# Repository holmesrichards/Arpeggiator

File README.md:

# ArpeggiatorModule
Code and hardware for Kosmo/Eurorack arpeggiator module

This is an arpeggiator based on a variant of the [dacarduino](https://github.com/holmesrichards/dacarduino) board. As such it uses the dacarduino library as well as the Arpeggiator library in this repository.

Design is for Kosmo format module but the PCB and code would work equally well for a Eurorack version. It would just need a smaller front panel. Shorter anyway, maybe wider.

THIS IS A WORK IN PROGRESS.

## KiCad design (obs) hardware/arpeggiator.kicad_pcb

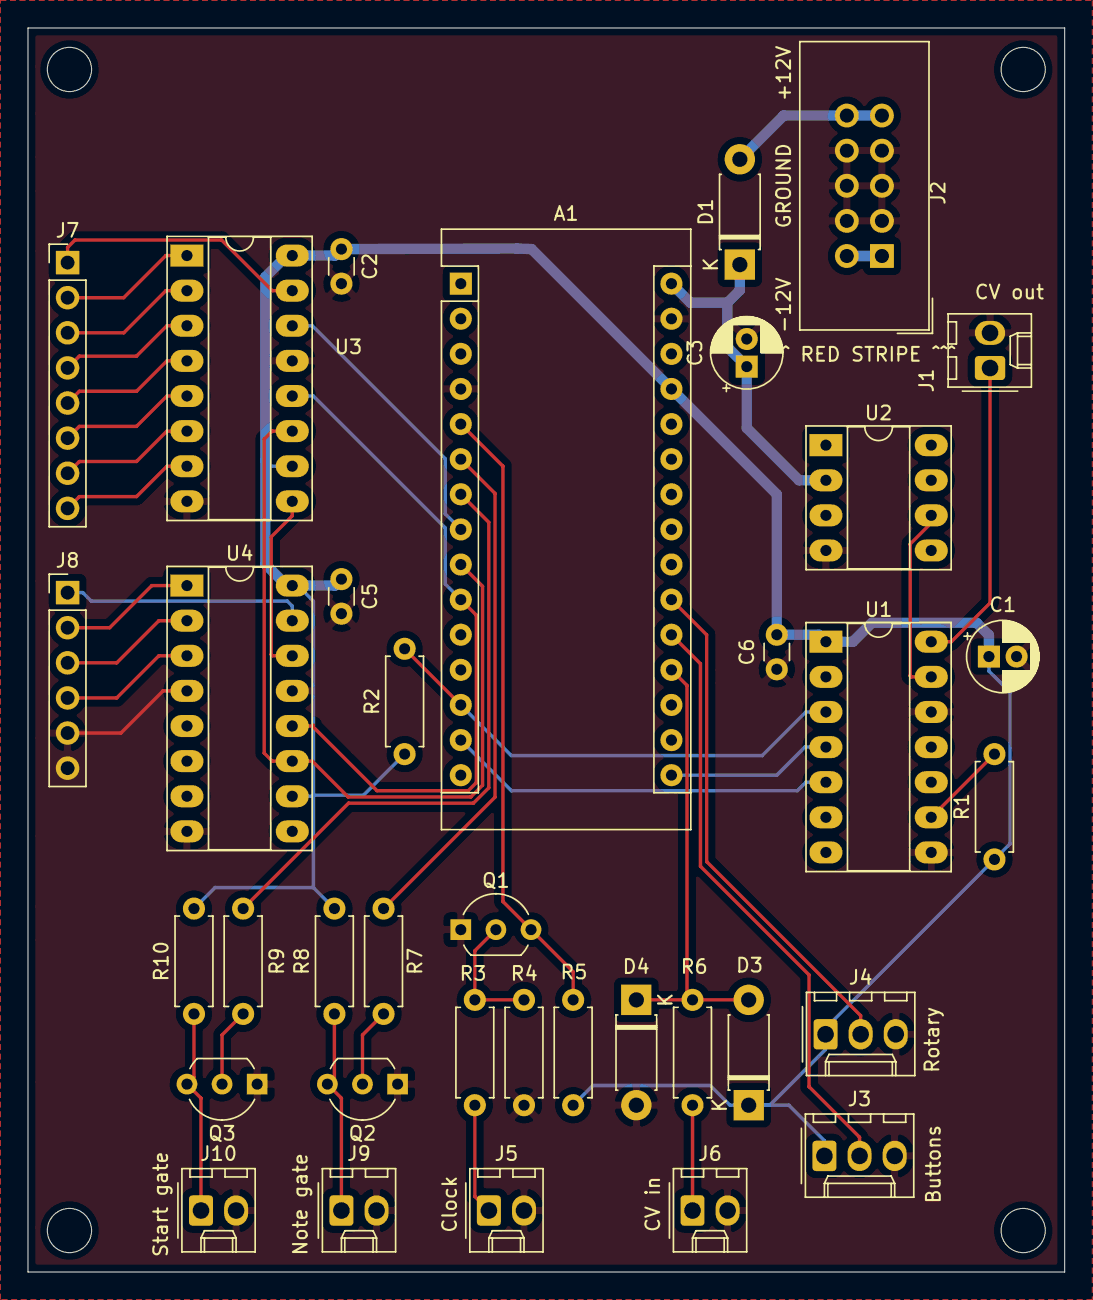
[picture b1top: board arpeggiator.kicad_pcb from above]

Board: 2 copper layers, 75.0 x 90.0 mm, 40 parts (0 on the bottom side), 41 nets.

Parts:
A1: Arduino_Nano_v3.x 5V; Arduino_Nano
C1, C3: 10uF; CP_Radial_D5.0mm_P2.00mm
C2, C5, C6: 0.1uF; C_Disc_D3.0mm_W1.6mm_P2.50mm
D1, D3, D4: 1N5817; D_DO-41_SOD81_P7.62mm_Horizontal
H1, H2, H3, H4: MountingHole; MountingHole_3.2mm_M3
J1: CV_OUT; Molex_KK-254_AE-6410-02A_1x02_P2.54mm_Vertical
J2: EURO_PWR_2x5; IDC-Header_2x05_P2.54mm_Vertical
J3: BUTTONS; Molex_KK-254_AE-6410-03A_1x03_P2.54mm_Vertical
J4: ROTARY; Molex_KK-254_AE-6410-03A_1x03_P2.54mm_Vertical
J5: GATE IN; Molex_KK-254_AE-6410-02A_1x02_P2.54mm_Vertical
J6: CV IN; Molex_KK-254_AE-6410-02A_1x02_P2.54mm_Vertical
J7: Conn_01x08; PinHeader_1x08_P2.54mm_Vertical
J8: Conn_01x06; PinHeader_1x06_P2.54mm_Vertical
J9: Note gate; Molex_KK-254_AE-6410-02A_1x02_P2.54mm_Vertical
J10: Start gate; Molex_KK-254_AE-6410-02A_1x02_P2.54mm_Vertical
Q1, Q2, Q3: 2N3904; TO-92_Inline_Wide
R1, R2: 10K; R_Axial_DIN0207_L6.3mm_D2.5mm_P7.62mm_Horizontal
R3: 100k; R_Axial_DIN0207_L6.3mm_D2.5mm_P7.62mm_Horizontal
R4: 1M; R_Axial_DIN0207_L6.3mm_D2.5mm_P7.62mm_Horizontal
R5: 10k; R_Axial_DIN0207_L6.3mm_D2.5mm_P7.62mm_Horizontal
R6, R7, R8, R9, R10: 1k; R_Axial_DIN0207_L6.3mm_D2.5mm_P7.62mm_Horizontal
U1: MCP4922; DIP-14_W7.62mm_Socket_LongPads
U2: REF02CP+; DIP-8_W7.62mm_Socket_LongPads
U3, U4: 74HC595; DIP-16_W7.62mm_Socket_LongPads

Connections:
+VIN: A1.30, C3.1, D1.1, U2.2
/Arduino/A0: A1.19, D3.2, D4.1, R6.1
/Arduino/A1: A1.20, J3.2
/Arduino/A2: A1.21, J4.2
/Arduino/D2: A1.5, Q1.3, R5.1
/Arduino/D3: A1.6, R7.2
/Arduino/D4: A1.7, R9.2
/Arduino/D5: A1.8, U3.14
/Arduino/D6: A1.9, U3.11, U4.11
/Arduino/D7: A1.10, U3.12, U4.12
/Arduino/DAC_CS: A1.13, R2.2, U1.3
/Arduino/MOSI: A1.14, U1.5
/Arduino/SCK: A1.16, U1.4
/DAC/CV_OUT: J1.1, U1.14
/Digital out/NOTE_GATE: J9.1, Q2.3, R8.1
/Digital out/START_GATE: J10.1, Q3.3, R10.1
/Inputs/CV in/CV_IN: J6.1, R6.2
/Inputs/Clock in/GATE_IN: J5.1, R3.2
/Voltage reference/VREF: U1.13, U2.6
GND: A1.4, A1.29, C1.2, C2.2, C3.2, C5.2, C6.2, D4.2, J1.2, J2.3, J2.4, J2.5, J2.6, J2.7, J2.8, J3.3, J4.3, J5.2, J6.2, J8.6, J9.2, J10.2, Q1.1, Q2.1, Q3.1, R4.1, U1.8, U1.12, U2.4, U3.8, U3.13, U4.8, U4.13
unnamed: D1.2, J2.9, J2.10
unnamed: J2.1, J2.2
unnamed: J7.1, U3.15
unnamed: J7.2, U3.1
unnamed: J7.3, U3.2
unnamed: J7.4, U3.3
unnamed: J7.5, U3.4
unnamed: J7.6, U3.5
unnamed: J7.7, U3.6
unnamed: J7.8, U3.7
unnamed: J8.1, U4.15
unnamed: J8.2, U4.1
unnamed: J8.3, U4.2
unnamed: J8.4, U4.3
unnamed: J8.5, U4.4
unnamed: Q1.2, R3.1, R4.2
unnamed: Q2.2, R7.1
unnamed: Q3.2, R9.1
unnamed: R1.2, U1.9
unnamed: U3.9, U4.14
VCC: A1.27, C1.1, C2.1, C5.1, C6.1, D3.1, J3.1, J4.1, R1.1, R2.1, R5.2, R8.2, R10.2, U1.1, U3.10, U3.16, U4.10, U4.16

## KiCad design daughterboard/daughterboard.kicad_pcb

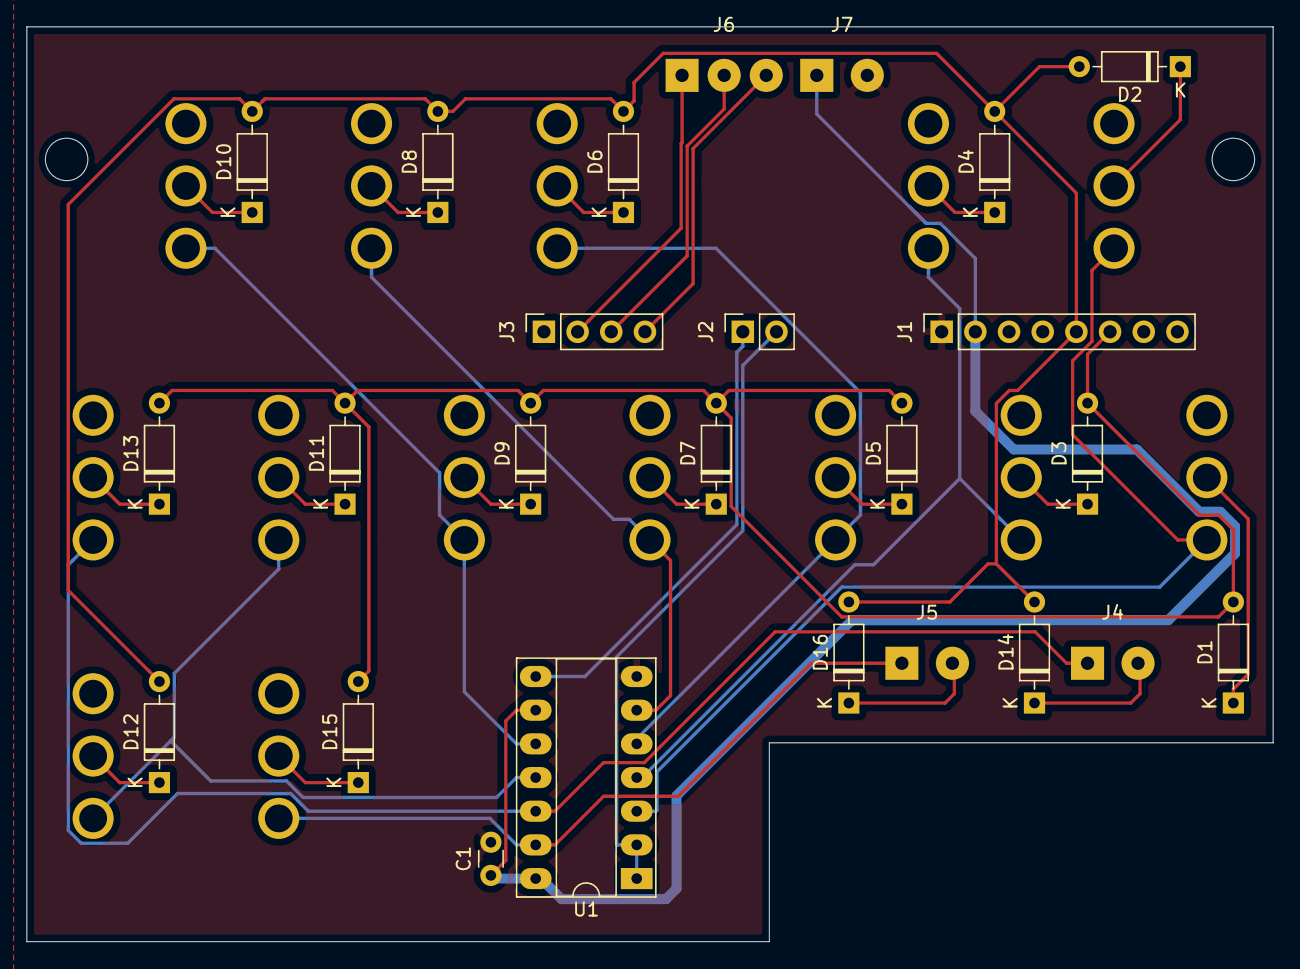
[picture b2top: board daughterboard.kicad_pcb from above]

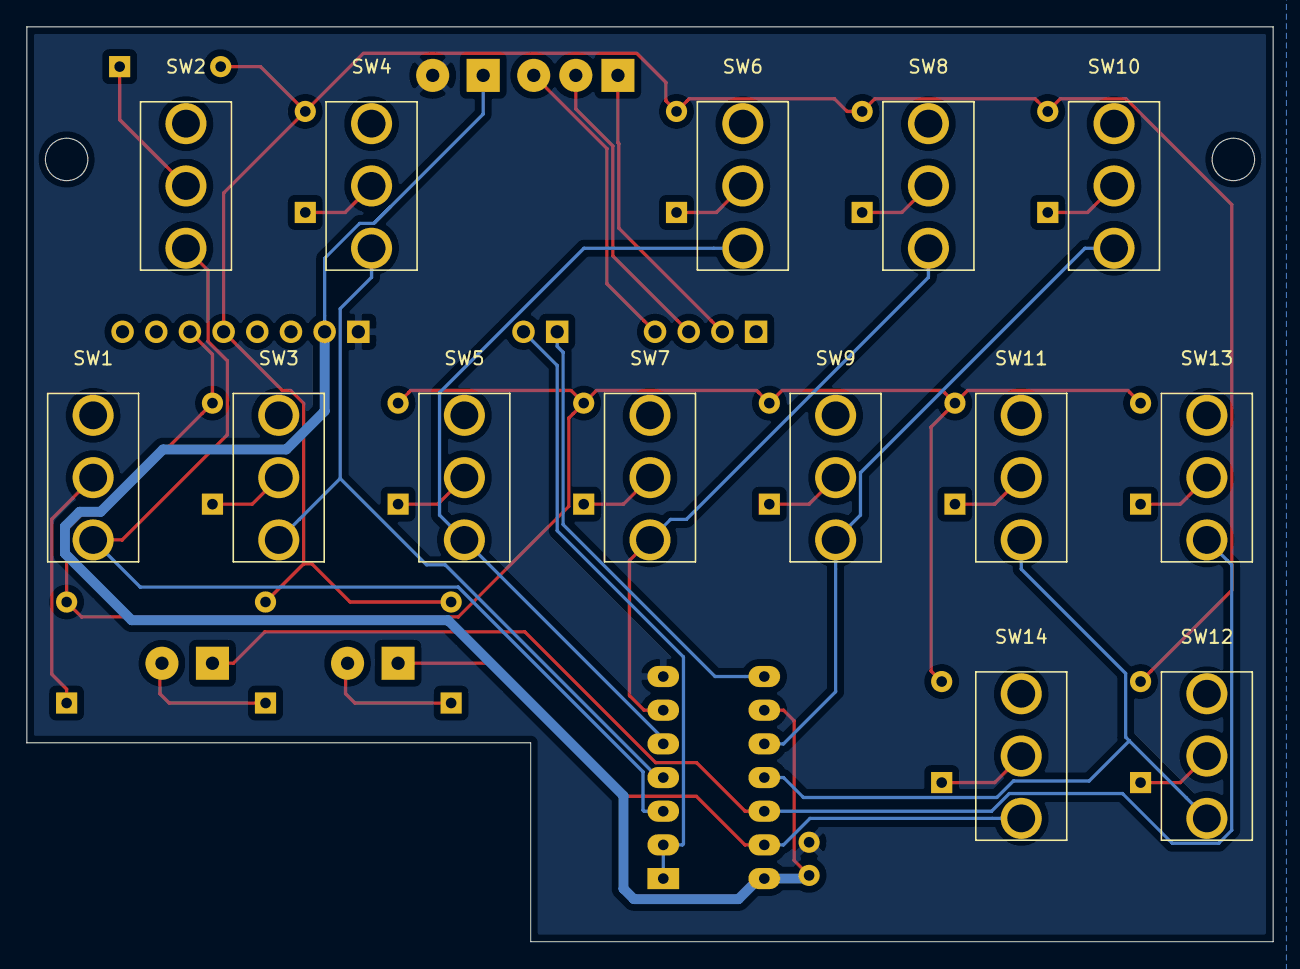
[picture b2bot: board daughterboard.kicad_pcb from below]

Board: 2 copper layers, 94.0 x 69.0 mm, 41 parts (14 on the bottom side), 33 nets.

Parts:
C1: 100nF; C_Disc_D3.0mm_W1.6mm_P2.50mm
D1, D2, D3, D4, D5, D6, D7, D8, D9, D10, D11, D12, D13, D14, D15, D16: 1N4148; D_DO-35_SOD27_P7.62mm_Horizontal
H1, H2: MountingHole; MountingHole_3.2mm_M3
J1: Conn_01x08; PinSocket_1x08_P2.54mm_Vertical
J2: Conn_01x02; PinSocket_1x02_P2.54mm_Vertical
J3: Conn_01x04; PinSocket_1x04_P2.54mm_Vertical
J4, J5, J7: Conn_01x02; SolderWirePad_1x02_P3.81mm_Drill1mm
J6: Conn_01x05; SolderWirePad_1x03_P3.175mm_Drill1mm
SW1, SW2, SW3, SW4, SW5, SW6, SW7, SW8, SW9, SW10, SW11, SW12, SW13, SW14: SW_SPST; SPDT-toggle-switch-1M-series
U1: 74HC164; DIP-14_W7.62mm_Socket_LongPads

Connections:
/A4: J3.4, J6.3
/A5: J3.3, J6.2
/A6: J3.2, J6.1
/D8: J2.1, U1.8
/D9: J2.2, U1.1, U1.2
/GATE_IN_C: D1.2, D3.2, D5.2, D7.2, D9.2, D11.2, D13.2, D15.2, J1.6
/GATE_IN_D: D2.2, D4.2, D6.2, D8.2, D10.2, D12.2, D14.2, D16.2, J1.5
/RS1: J5.1, SW14.1, U1.13
/RS2: D16.1, J5.2
/SS1: J4.1, SW13.1, U1.12
/SS2: D14.1, J4.2
GND: C1.2, J1.1, J7.2, U1.7
unnamed: D1.1, SW1.2
unnamed: D2.1, SW2.2
unnamed: D3.1, SW3.2
unnamed: D4.1, SW4.2
unnamed: D5.1, SW5.2
unnamed: D6.1, SW6.2
unnamed: D7.1, SW7.2
unnamed: D8.1, SW8.2
unnamed: D9.1, SW9.2
unnamed: D10.1, SW10.2
unnamed: D11.1, SW11.2
unnamed: D12.1, SW12.2
unnamed: D13.1, SW13.2
unnamed: D15.1, SW14.2
unnamed: SW1.1, SW2.1, U1.3
unnamed: SW3.1, SW4.1, U1.4
unnamed: SW5.1, SW6.1, U1.5
unnamed: SW7.1, SW8.1, U1.6
unnamed: SW9.1, SW10.1, U1.10
unnamed: SW11.1, SW12.1, U1.11
VCC: C1.1, J1.2, J7.1, U1.9, U1.14

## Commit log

2020-04-24 Initial version
2020-09-01 Lots of updates belatedly committed
2021-01-02 Revised plans
2021-01-17 Include lib table files
